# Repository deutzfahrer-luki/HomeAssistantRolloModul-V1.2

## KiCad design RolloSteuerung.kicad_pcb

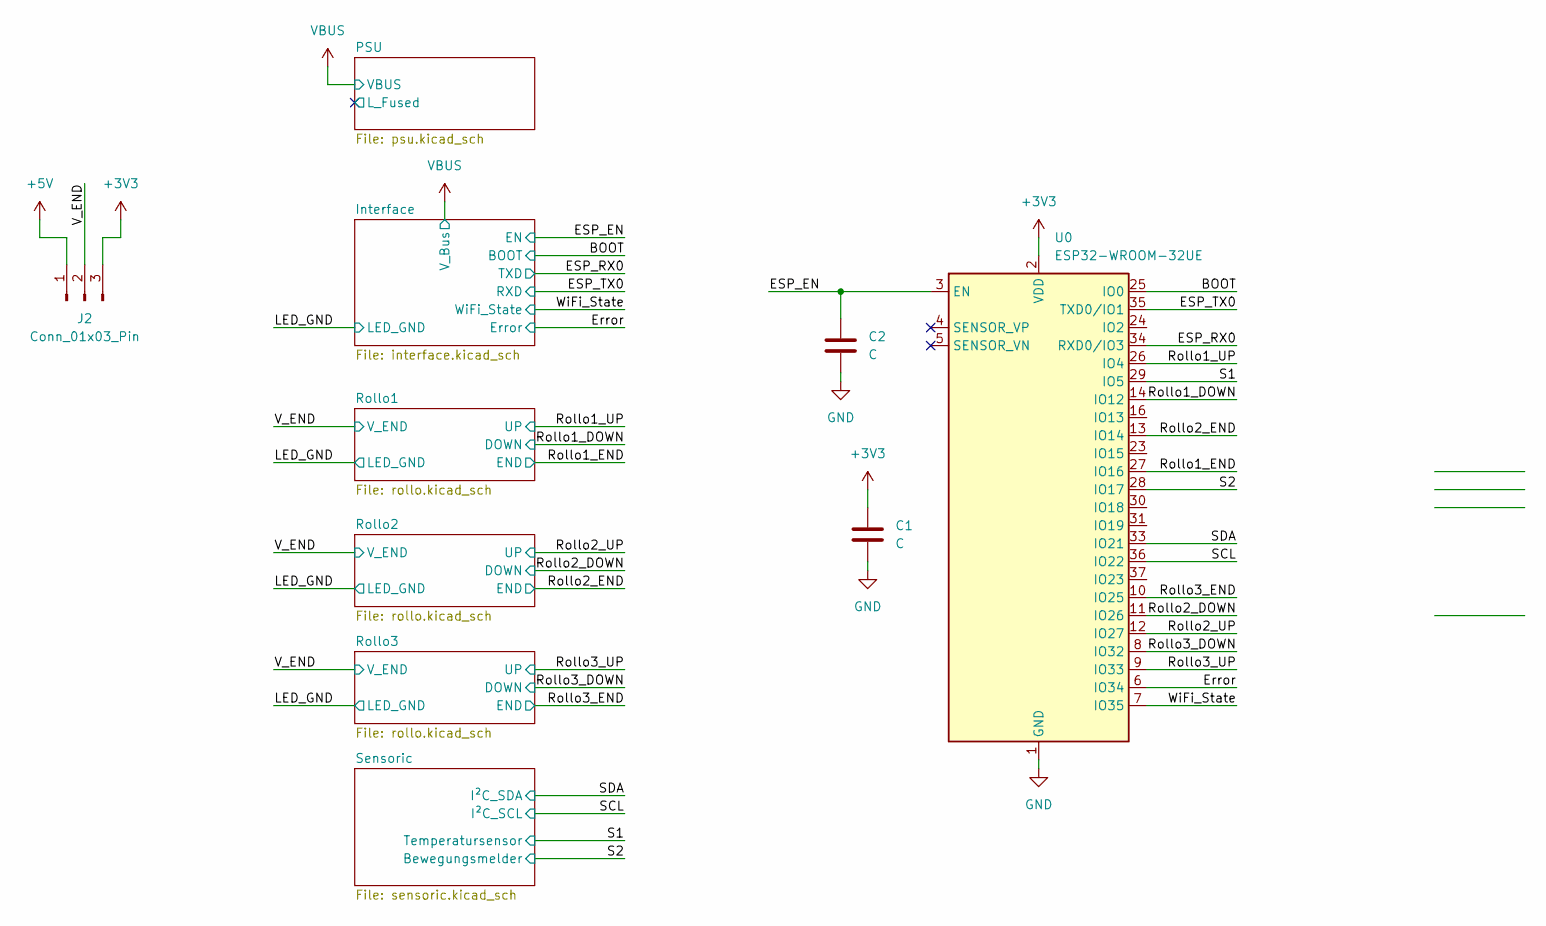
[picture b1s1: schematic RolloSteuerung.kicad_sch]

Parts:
C1, C2: C
J2: Conn_01x03_Pin; PinHeader_1x03_P2.54mm_Vertical
U0: ESP32-WROOM-32UE

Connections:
+3V3: C1.1, J2.3, U0.2 (VDD); also elsewhere on the board
+5V: J2.1; also elsewhere on the board
/BOOT: U0.25 (IO0); also elsewhere on the board
/ESP_EN: C2.1, U0.3 (EN); also elsewhere on the board
/ESP_RX0: U0.34 (RXD0/IO3); also elsewhere on the board
/ESP_TX0: U0.35 (TXD0/IO1); also elsewhere on the board
/Error: U0.6 (IO34); also elsewhere on the board
/Rollo1_DOWN: U0.14 (IO12); also elsewhere on the board
/Rollo1_END: U0.27 (IO16); also elsewhere on the board
/Rollo1_UP: U0.26 (IO4); also elsewhere on the board
/Rollo2_DOWN: U0.11 (IO26); also elsewhere on the board
/Rollo2_END: U0.13 (IO14); also elsewhere on the board
/Rollo2_UP: U0.12 (IO27); also elsewhere on the board
/Rollo3_DOWN: U0.8 (IO32); also elsewhere on the board
/Rollo3_END: U0.10 (IO25); also elsewhere on the board
/Rollo3_UP: U0.9 (IO33); also elsewhere on the board
/S1: U0.29 (IO5); also elsewhere on the board
/S2: U0.28 (IO17); also elsewhere on the board
/SCL: U0.36 (IO22); also elsewhere on the board
/SDA: U0.33 (IO21); also elsewhere on the board
/V_END: J2.2; also elsewhere on the board
/WiFi_State: U0.7 (IO35); also elsewhere on the board
GND: C1.2, C2.2, U0.1 (GND), U0.15 (GND), U0.38 (GND), U0.39 (GND); also elsewhere on the board

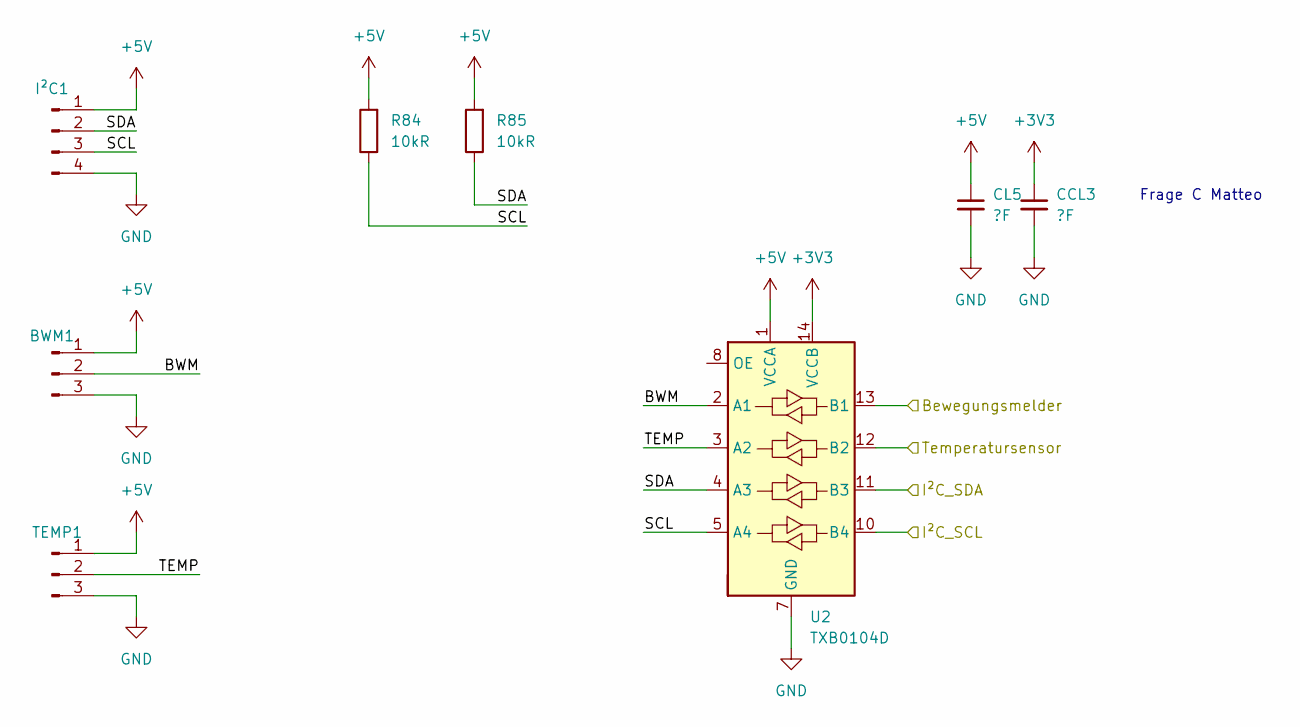
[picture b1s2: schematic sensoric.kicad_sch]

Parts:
BWM1: Conn_01x03_Pin; JST-XH-03-PACKAGE-LONG-PAD
CCL3: ?F; C_1206_3216Metric_Pad1.33x1.80mm_HandSolder
CL5: ?F; C_1206_3216Metric_Pad1.33x1.80mm_HandSolder
I²C1: Conn_01x04_Pin; JST-XH-04-PACKAGE-LONG-PAD
R84, R85: 10kR; R_1206_3216Metric_Pad1.30x1.75mm_HandSolder
TEMP1: Conn_01x03_Pin; JST-XH-03-PACKAGE-LONG-PAD
U2: TXB0104D; SOIC-14_3.9x8.7mm_P1.27mm

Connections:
+3V3: CCL3.1, U2.14 (VCCB); also elsewhere on the board
+5V: BWM1.1, CL5.1, I²C1.1, R84.2, R85.2, TEMP1.1, U2.1 (VCCA); also elsewhere on the board
/S1: U2.12 (B2); also elsewhere on the board
/S2: U2.13 (B1); also elsewhere on the board
/SCL: U2.10 (B4); also elsewhere on the board
/SDA: U2.11 (B3); also elsewhere on the board
/Sensoric/BWM: BWM1.2, U2.2 (A1)
/Sensoric/SCL: I²C1.3, R84.1, U2.5 (A4)
/Sensoric/SDA: I²C1.2, R85.1, U2.4 (A3)
/Sensoric/TEMP: TEMP1.2, U2.3 (A2)
GND: BWM1.3, CCL3.2, CL5.2, I²C1.4, TEMP1.3, U2.7 (GND); also elsewhere on the board

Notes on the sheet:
Frage C Matteo

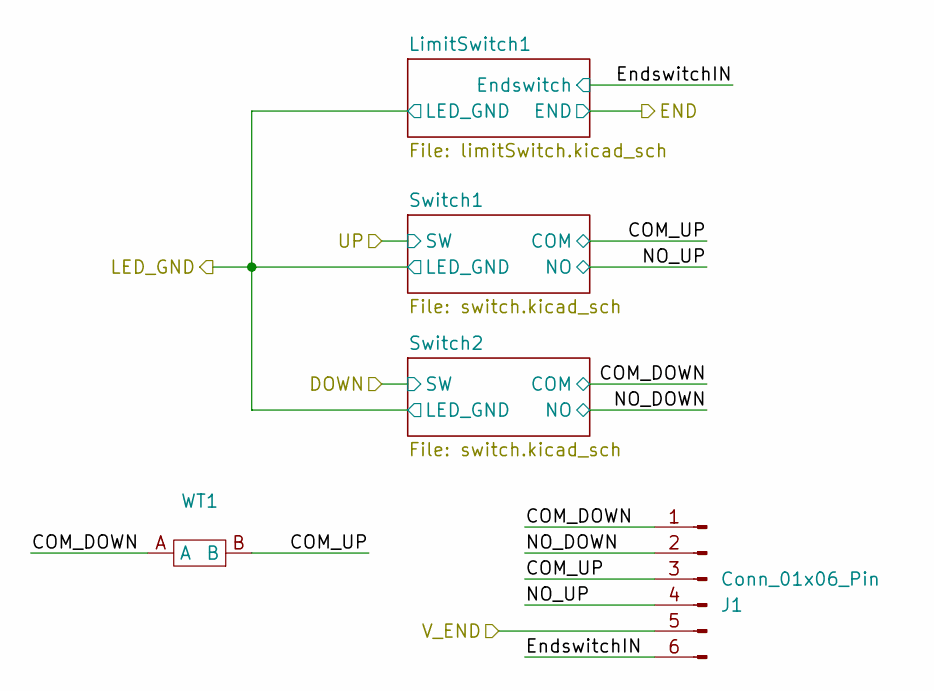
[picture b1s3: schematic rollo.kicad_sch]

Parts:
J1: Conn_01x06_Pin; PhoenixContact_MSTBA_2,5_6-G-5,08_1x06_P5.08mm_Horizontal
WT1: Bridge

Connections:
/Rollo1/COM_DOWN: J1.1; also elsewhere on the board
/Rollo1/COM_UP: J1.3; also elsewhere on the board
/Rollo1/EndswitchIN: J1.6; also elsewhere on the board
/Rollo1/NO_DOWN: J1.2; also elsewhere on the board
/Rollo1/NO_UP: J1.4; also elsewhere on the board
/V_END: J1.5; also elsewhere on the board

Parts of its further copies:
J3, J12: Conn_01x06_Pin; PhoenixContact_MSTBA_2,5_6-G-5,08_1x06_P5.08mm_Horizontal

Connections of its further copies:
/Rollo2/COM_DOWN: J3.1; also elsewhere on the board
/Rollo2/COM_UP: J3.3; also elsewhere on the board
/Rollo2/EndswitchIN: J3.6; also elsewhere on the board
/Rollo2/NO_DOWN: J3.2; also elsewhere on the board
/Rollo2/NO_UP: J3.4; also elsewhere on the board
/Rollo3/COM_DOWN: J12.1; also elsewhere on the board
/Rollo3/COM_UP: J12.3; also elsewhere on the board
/Rollo3/EndswitchIN: J12.6; also elsewhere on the board
/Rollo3/NO_DOWN: J12.2; also elsewhere on the board
/Rollo3/NO_UP: J12.4; also elsewhere on the board
/V_END: J3.5, J12.5; also elsewhere on the board

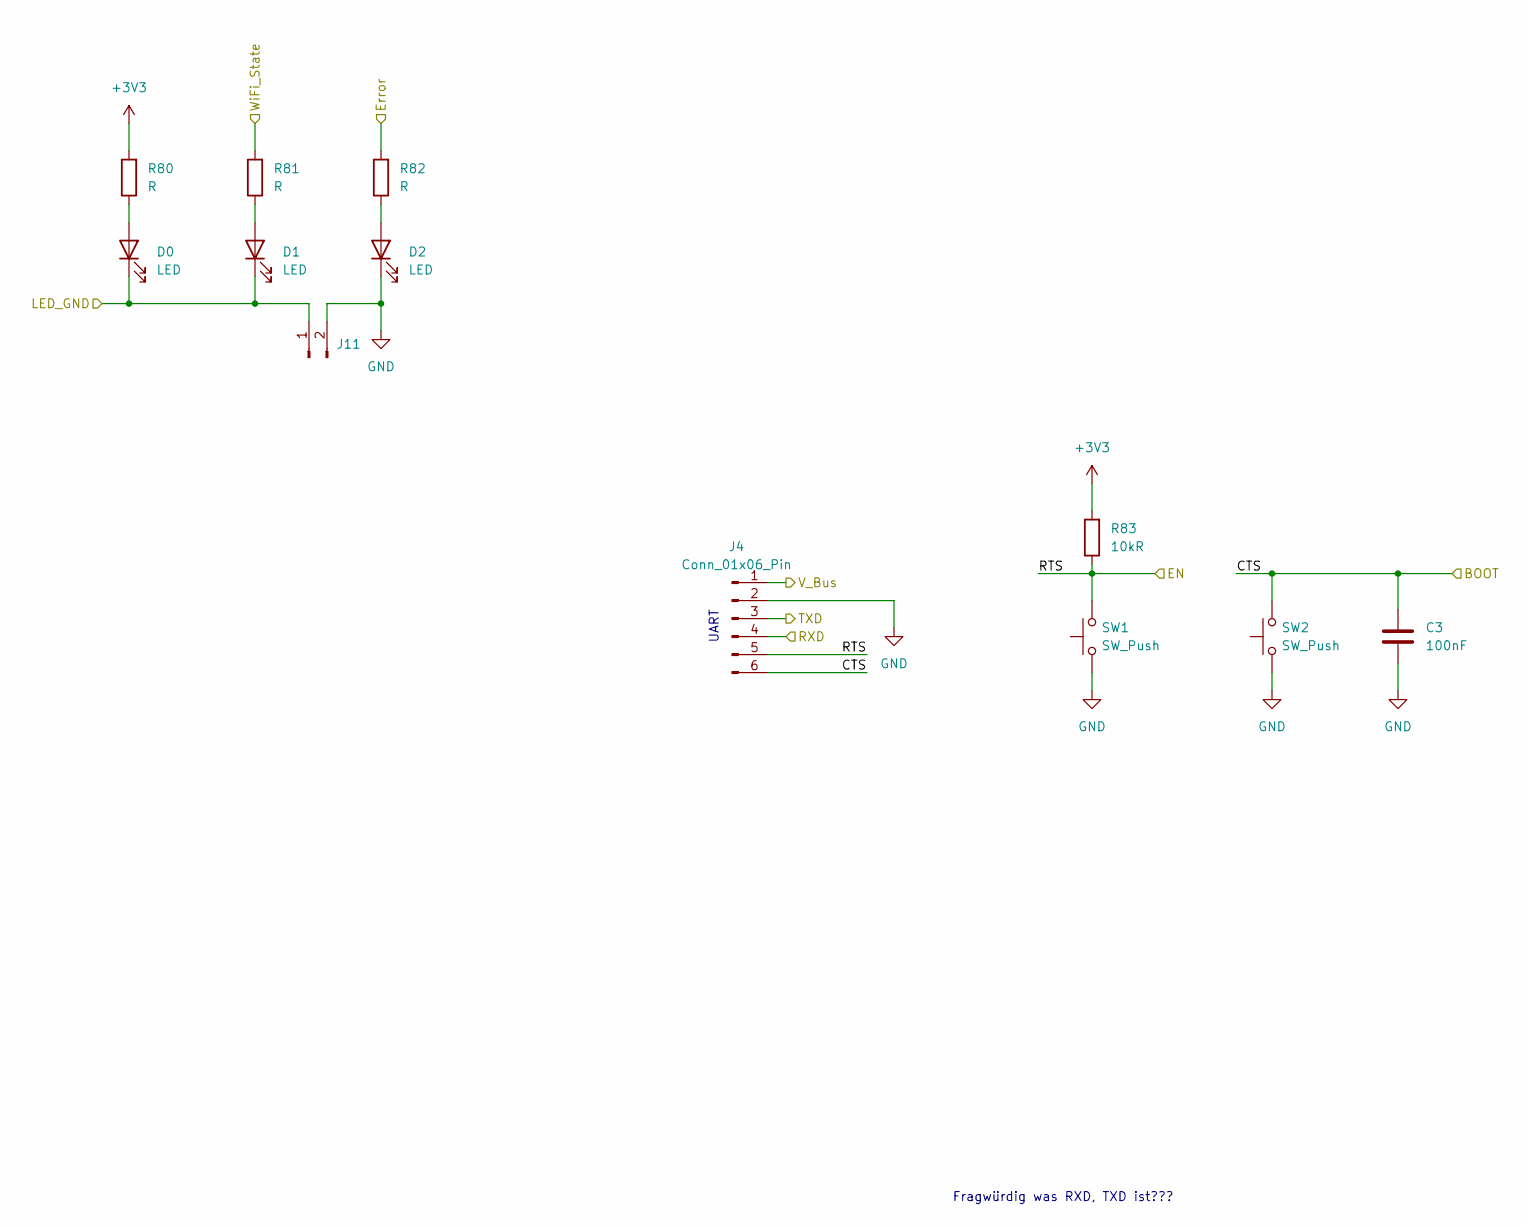
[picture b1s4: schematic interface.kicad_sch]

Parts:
C3: 100nF; C_1206_3216Metric_Pad1.33x1.80mm_HandSolder
D0, D1, D2: LED; LED_D3.0mm
J4: Conn_01x06_Pin; JST-XH-06-PACKAGE-LONG-PAD
J11: Conn_01x02_Pin; PinHeader_1x02_P2.54mm_Vertical
R80, R81, R82: R; R_1206_3216Metric_Pad1.30x1.75mm_HandSolder
R83: 10kR; R_1206_3216Metric_Pad1.30x1.75mm_HandSolder
SW1, SW2: SW_Push; SW_PUSH_6mm_H13mm

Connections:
+3V3: R80.2, R83.2; also elsewhere on the board
/BOOT: C3.1, J4.6, SW2.2; also elsewhere on the board
/ESP_EN: J4.5, R83.1, SW1.2; also elsewhere on the board
/ESP_RX0: J4.3; also elsewhere on the board
/ESP_TX0: J4.4; also elsewhere on the board
/Error: R82.2; also elsewhere on the board
/LED_GND: D0.1 (K), D1.1 (K), J11.1
/WiFi_State: R81.2; also elsewhere on the board
GND: C3.2, D2.1 (K), J4.2, J11.2, SW1.1, SW2.1; also elsewhere on the board
unnamed: D0.2 (A), R80.1
unnamed: D1.2 (A), R81.1
unnamed: D2.2 (A), R82.1
VBUS: J4.1; also elsewhere on the board

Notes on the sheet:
UART
Fragwürdig was RXD, TXD ist???

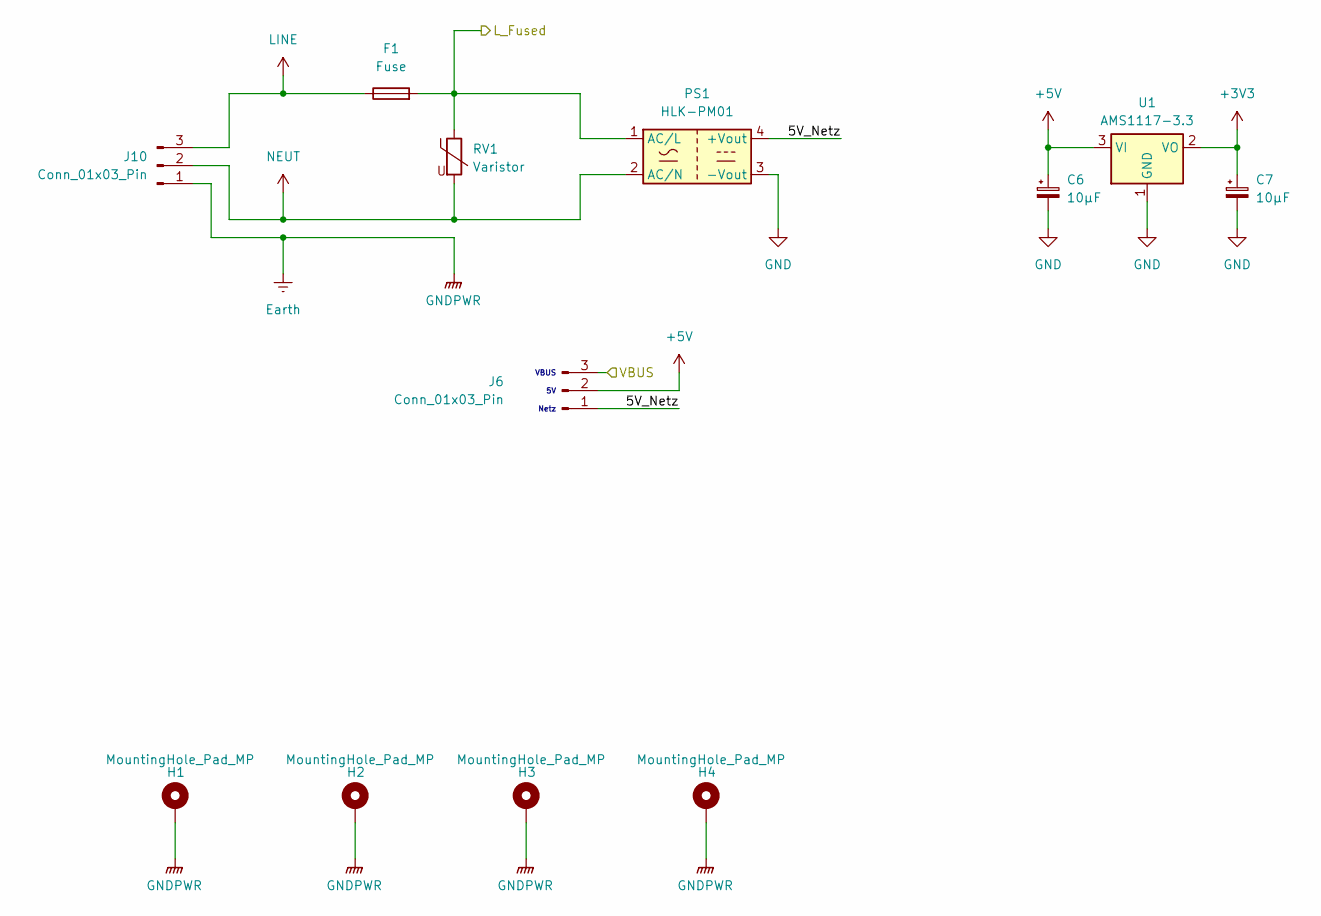
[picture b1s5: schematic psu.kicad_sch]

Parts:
C6, C7: 10µF; CP_Radial_D8.0mm_P3.80mm
F1: Fuse; Fuseholder_Clip-5x20mm_Bel_FC-203-22_Lateral_P17.80x5.00mm_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
H1, H2, H3, H4: MountingHole_Pad_MP; MountingHole_3.2mm_M3_Pad_Via
J6: Conn_01x03_Pin; PinHeader_1x03_P2.54mm_Vertical
J10: Conn_01x03_Pin; PhoenixContact_MSTBA_2,5_3-G-5,08_1x03_P5.08mm_Horizontal
PS1: HLK-PM01; Converter_ACDC_Hi-Link_HLK-PMxx
RV1: Varistor; RV_Disc_D9mm_W3.3mm_P5mm
U1: AMS1117-3.3; SOT-223-3_TabPin2

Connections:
+3V3: C7.1, U1.2 (VO); also elsewhere on the board
+5V: C6.1, J6.2, U1.3 (VI); also elsewhere on the board
/PSU/5V_Netz: J6.1, PS1.4 (+Vout)
/PSU/L_Fused: F1.2, PS1.1 (AC/L), RV1.1
Earth: H1.MP, H2.MP, H3.MP, H4.MP, J10.1
GND: C6.2, C7.2, PS1.3 (-Vout), U1.1 (GND); also elsewhere on the board
LINE: F1.1, J10.3
NEUT: J10.2, PS1.2 (AC/N), RV1.2
VBUS: J6.3; also elsewhere on the board

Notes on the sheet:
VBUS
Netz

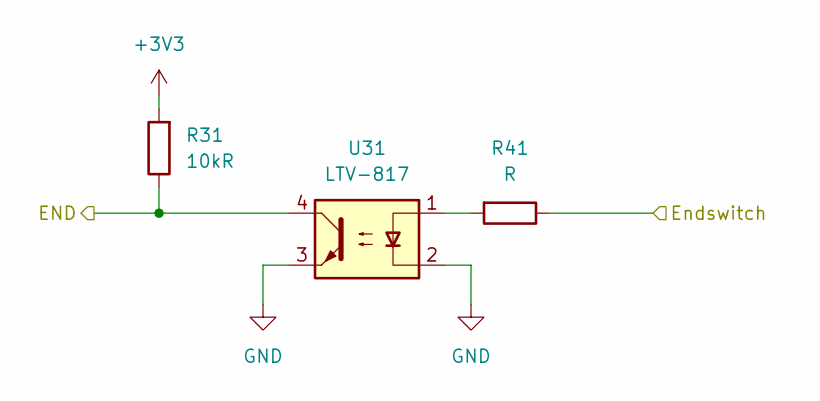
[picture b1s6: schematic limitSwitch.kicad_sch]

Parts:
R31: 10kR; R_1206_3216Metric_Pad1.30x1.75mm_HandSolder
R41: R; R_1206_3216Metric_Pad1.30x1.75mm_HandSolder
U31: LTV-817; DIP-4_W7.62mm

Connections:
+3V3: R31.2; also elsewhere on the board
/Rollo1/EndswitchIN: R41.1; also elsewhere on the board
/Rollo1_END: R31.1, U31.4; also elsewhere on the board
GND: U31.2, U31.3; also elsewhere on the board
unnamed: R41.2, U31.1

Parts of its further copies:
R32, R33: 10kR; R_1206_3216Metric_Pad1.30x1.75mm_HandSolder
R42, R43: R; R_1206_3216Metric_Pad1.30x1.75mm_HandSolder
U32, U33: LTV-817; DIP-4_W7.62mm

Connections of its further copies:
+3V3: R32.2, R33.2; also elsewhere on the board
/Rollo2/EndswitchIN: R42.1; also elsewhere on the board
/Rollo2_END: R32.1, U32.4; also elsewhere on the board
/Rollo3/EndswitchIN: R43.1; also elsewhere on the board
/Rollo3_END: R33.1, U33.4; also elsewhere on the board
GND: U32.2, U32.3, U33.2, U33.3; also elsewhere on the board
unnamed: R42.2, U32.1
unnamed: R43.2, U33.1

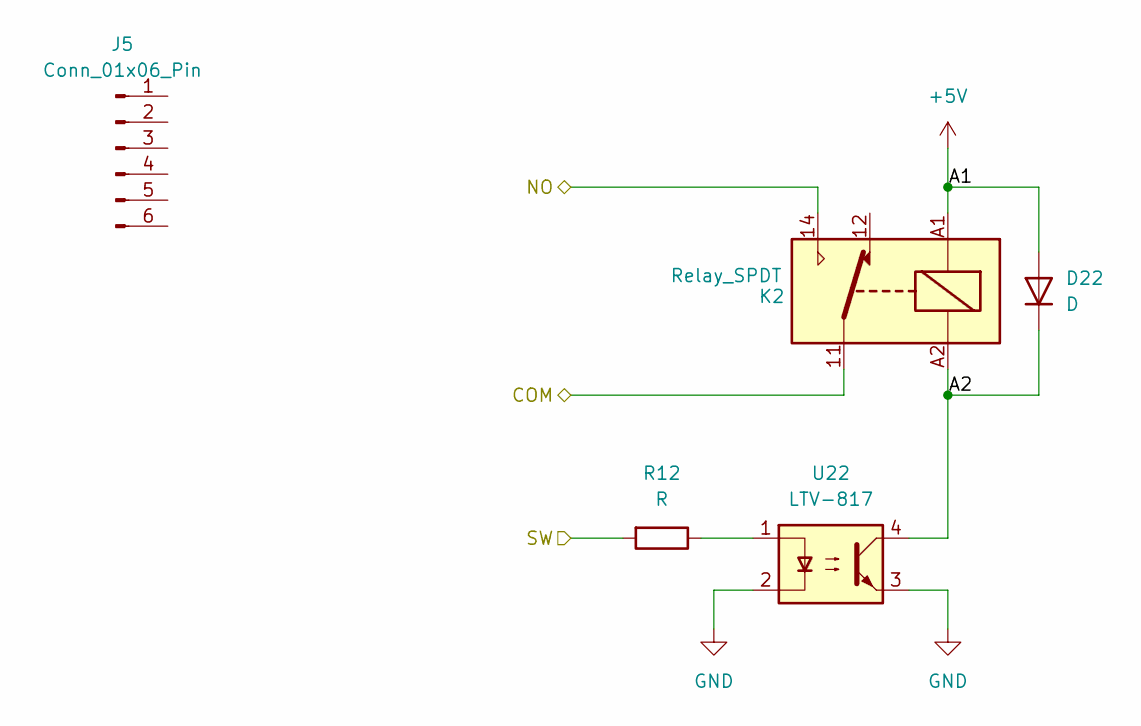
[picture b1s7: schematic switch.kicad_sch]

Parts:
D22: D; D_MiniMELF
J5: Conn_01x06_Pin
K2: Relay_SPDT; AZ6991-1C5-DE
R12: R; R_1206_3216Metric_Pad1.30x1.75mm_HandSolder
U22: LTV-817; DIP-4_W7.62mm

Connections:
+5V: D22.2 (A), K2.A1; also elsewhere on the board
/Rollo1/COM_DOWN: K2.11; also elsewhere on the board
/Rollo1/NO_DOWN: K2.14; also elsewhere on the board
/Rollo1/Switch2/A2: D22.1 (K), K2.A2, U22.4
/Rollo1_DOWN: R12.2; also elsewhere on the board
GND: U22.2, U22.3; also elsewhere on the board
unnamed: R12.1, U22.1

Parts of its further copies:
D21, D23, D24, D25, D26: D; D_MiniMELF
K1, K3, K4, K5, K6: Relay_SPDT; AZ6991-1C5-DE
R11, R13, R14, R15, R16: R; R_1206_3216Metric_Pad1.30x1.75mm_HandSolder
U21, U23, U24, U25, U26: LTV-817; DIP-4_W7.62mm

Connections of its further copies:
+5V: D21.2 (A), D23.2 (A), D24.2 (A), D25.2 (A), D26.2 (A), K1.A1, K3.A1, K4.A1, K5.A1, K6.A1; also elsewhere on the board
/Rollo1/COM_UP: K1.11; also elsewhere on the board
/Rollo1/NO_UP: K1.14; also elsewhere on the board
/Rollo1/Switch1/A2: D21.1 (K), K1.A2, U21.4
/Rollo1_UP: R11.2; also elsewhere on the board
/Rollo2/COM_DOWN: K4.11; also elsewhere on the board
/Rollo2/COM_UP: K3.11; also elsewhere on the board
/Rollo2/NO_DOWN: K4.14; also elsewhere on the board
/Rollo2/NO_UP: K3.14; also elsewhere on the board
/Rollo2/Switch1/A2: D24.1 (K), K3.A2, U23.4
/Rollo2/Switch2/A2: D23.1 (K), K4.A2, U24.4
/Rollo2_DOWN: R14.2; also elsewhere on the board
/Rollo2_UP: R13.2; also elsewhere on the board
/Rollo3/COM_DOWN: K6.11; also elsewhere on the board
/Rollo3/COM_UP: K5.11; also elsewhere on the board
/Rollo3/NO_DOWN: K6.14; also elsewhere on the board
/Rollo3/NO_UP: K5.14; also elsewhere on the board
/Rollo3/Switch1/A2: D26.1 (K), K5.A2, U25.4
/Rollo3/Switch2/A2: D25.1 (K), K6.A2, U26.4
/Rollo3_DOWN: R16.2; also elsewhere on the board
/Rollo3_UP: R15.2; also elsewhere on the board
GND: U21.2, U21.3, U23.2, U23.3, U24.2, U24.3, U25.2, U25.3, U26.2, U26.3; also elsewhere on the board
unnamed: R11.1, U21.1
unnamed: R13.1, U23.1
unnamed: R14.1, U24.1
unnamed: R15.1, U25.1
unnamed: R16.1, U26.1

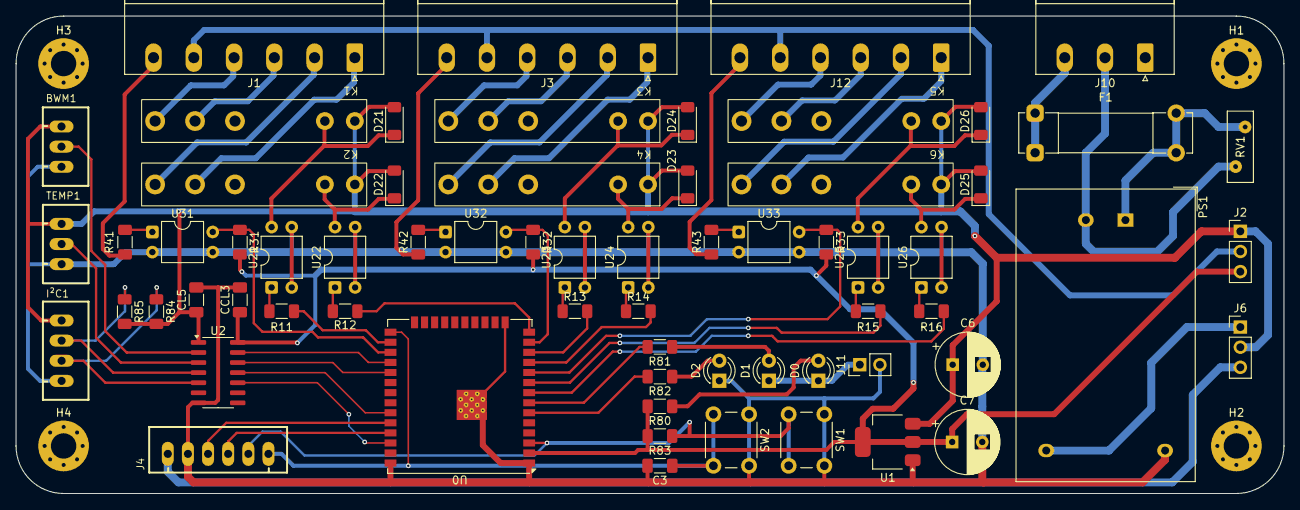
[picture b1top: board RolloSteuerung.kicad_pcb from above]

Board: 2 copper layers, 160.0 x 60.2 mm, 70 parts (0 on the bottom side), 66 nets.

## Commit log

2025-07-04 add pdf sch
